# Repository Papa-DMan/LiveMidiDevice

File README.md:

# LiveMidiDevice
This repo merges my personal MIDI-Controller-DisplayDriver and MIDI-Controller repositories into this public one and also hosts the schematics and pcb designs for the project

The MIDI-Controller uses a tree and node structure. A FRDMK64F Dev board is the root of the tree and can handle up to two nodes right now. It utilizes the I2C bus with an extender chipset from TI to send data and power over an RJ45 8 connector cable down to the nodes that contain up to 8 buttons and 1 expression pedal and 1 led display controlled by and stm32 l412kb dev board.

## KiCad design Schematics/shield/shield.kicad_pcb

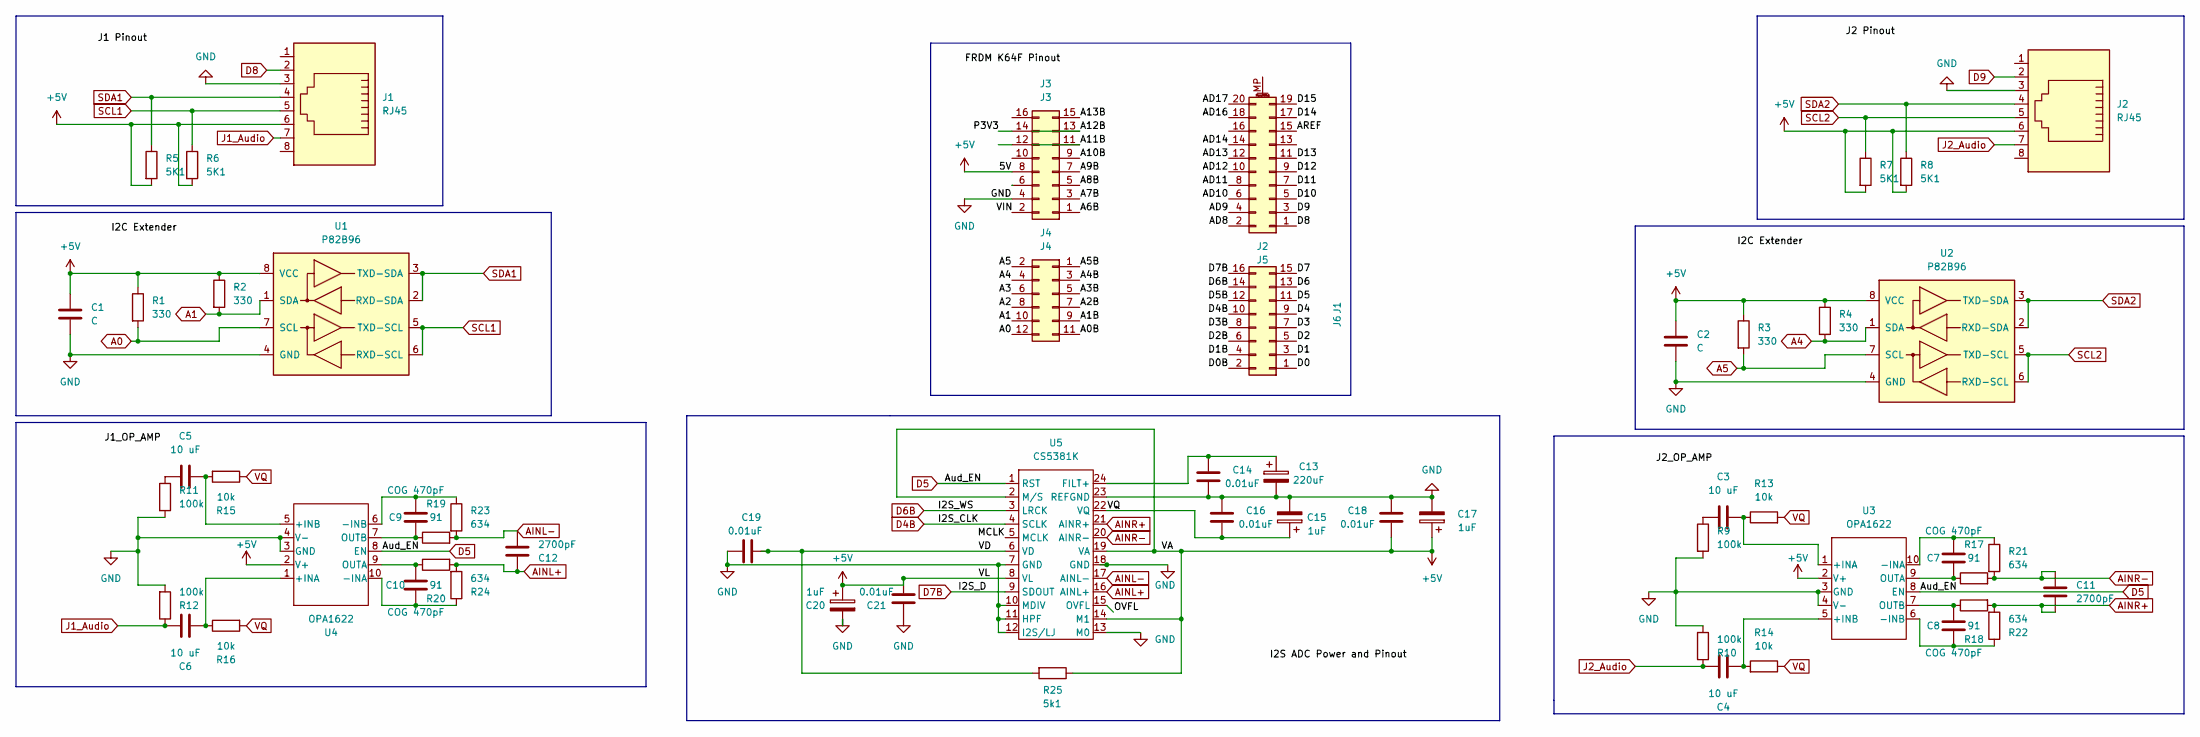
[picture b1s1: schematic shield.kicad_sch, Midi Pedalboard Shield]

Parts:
C1, C2: C; C_Disc_D3.0mm_W1.6mm_P2.50mm
C3, C4, C5, C6: 10 uF; CP_Radial_Tantal_D5.5mm_P5.00mm
C7, C8, C9, C10: COG 470pF; C_1812_4532Metric_Pad1.57x3.40mm_HandSolder
C11, C12: 2700pF; CP_Radial_D5.0mm_P2.50mm
C13: 220uF; C_1210_3225Metric_Pad1.33x2.70mm_HandSolder
C14, C16, C18, C19, C21: 0.01uF; C_0402_1005Metric_Pad0.74x0.62mm_HandSolder
C15, C17, C20: 1uF; C_0603_1608Metric_Pad1.08x0.95mm_HandSolder
J1, J2: RJ45; RJ45_Amphenol_RJHSE538X
J3: J3; PinHeader_2x08_P2.54mm_Vertical
J4: J4; PinHeader_2x06_P2.54mm_Vertical
J5: J2; PinHeader_2x10_P2.54mm_Vertical
J6: J1; PinHeader_2x08_P2.54mm_Vertical
R1, R2, R3, R4: 330; R_Axial_DIN0207_L6.3mm_D2.5mm_P2.54mm_Vertical
R5, R6, R7, R8: 5K1; R_Axial_DIN0207_L6.3mm_D2.5mm_P2.54mm_Vertical
R9, R10, R11, R12: 100k; R_Axial_DIN0207_L6.3mm_D2.5mm_P2.54mm_Vertical
R13, R14, R15, R16: 10k; R_Axial_DIN0207_L6.3mm_D2.5mm_P2.54mm_Vertical
R17, R18, R19, R20: 91; R_Axial_DIN0414_L11.9mm_D4.5mm_P5.08mm_Vertical
R21, R22, R23, R24: 634; R_1206_3216Metric_Pad1.30x1.75mm_HandSolder
R25: 5k1; R_Axial_DIN0207_L6.3mm_D2.5mm_P2.54mm_Vertical
U1, U2: P82B96; DIP-8_W7.62mm
U3, U4: OPA1622; Texas_S-PVSON-N10
U5: CS5381K; SOIC-24

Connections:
+5V: C1.1, C2.1, C17.1, C18.2, C20.1, C21.2, J1.6, J2.6, J3.8, R1.1, R2.1, R3.1, R4.1, R5.2, R6.2, R7.2, R8.2, R25.1, U1.8 (VCC), U2.8 (VCC), U3.2 (V+), U4.2 (V+), U5.2 (M/S), U5.8 (VL), U5.14 (M1), U5.19 (VA)
/A0B: J4.11
/A1B: J4.9
/A2: J4.8
/A2B: J4.7
/A3: J4.6
/A3B: J4.5
/A4B: J4.3
/A5B: J4.1
/A6B: J3.1
/A7B: J3.3
/A8B: J3.5
/A9B: J3.7
/A10B: J3.9
/A11B: J3.11
/A12B: J3.13
/A13B: J3.15
/AD8: J5.2
/AD9: J5.4
/AD10: J5.6
/AD11: J5.8
/AD12: J5.10
/AD13: J5.12
/AD14: J5.14
/AD16: J5.18
/AD17: J5.20
/AREF: J5.15
/D0: J6.1
/D0B: J6.2
/D1: J6.3
/D1B: J6.4
/D2: J6.5
/D2B: J6.6
/D3: J6.7
/D3B: J6.8
/D4: J6.9
/D5B: J6.12
/D6: J6.13
/D7: J6.15
/D10: J5.5
/D11: J5.7
/D12: J5.9
/D13: J5.11
/D14: J5.17
/D15: J5.19
/MCLK: U5.5 (MCLK)
/OVFL: U5.15 (OVFL)
/P3V3: J3.14
/VD: C19.1, R25.2, U5.6 (VD)
A0: J4.12, R1.2, U1.7 (SCL)
A1: J4.10, R2.2, U1.1 (SDA)
A4: J4.4, R4.2, U2.1 (SDA)
A5: J4.2, R3.2, U2.7 (SCL)
AINL+: C12.1, R20.2, R24.2, U5.16 (AINL+)
AINL-: C12.2, R19.2, R23.2, U5.17 (AINL-)
AINR+: C11.2, R18.2, R22.2, U5.21 (AINR+)
AINR-: C11.1, R17.2, R21.2, U5.20 (AINR-)
D4B: J6.10, U5.4 (SCLK)
D5: J6.11, U3.8 (EN), U4.8 (EN), U5.1 (RST)
D6B: J6.14, U5.3 (LRCK)
D7B: J6.16, U5.9 (SDOUT)
D8: J1.2, J5.1
D9: J2.2, J5.3
GND: C1.2, C2.2, C13.2, C14.2, C15.2, C16.1, C17.2, C18.1, C19.2, C20.2, C21.1, J1.3, J2.3, J3.4, R9.2, R10.2, R11.2, R12.2, U1.4 (GND), U2.4 (GND), U3.3 (GND), U3.4 (V-), U4.3 (GND), U4.4 (V-), U5.7 (GND), U5.10 (MDIV), U5.11 (HPF), U5.12 (I2S/LJ), U5.13 (M0), U5.18 (GND), U5.23 (REFGND)
J1_Audio: C6.1, J1.7, R12.1
J2_Audio: C4.1, J2.7, R10.1
unnamed: C3.1, R9.1
unnamed: C3.2, R13.1, U3.1 (+INA)
unnamed: C4.2, R14.2, U3.5 (+INB)
unnamed: C5.1, R11.1
unnamed: C5.2, R15.2, U4.5 (+INB)
unnamed: C6.2, R16.1, U4.1 (+INA)
unnamed: C7.1, R17.1, U3.9 (OUTA)
unnamed: C7.2, R21.1, U3.10 (-INA)
unnamed: C8.1, R18.1, U3.7 (OUTB)
unnamed: C8.2, R22.1, U3.6 (-INB)
unnamed: C9.1, R19.1, U4.7 (OUTB)
unnamed: C9.2, R23.1, U4.6 (-INB)
unnamed: C10.1, R20.1, U4.9 (OUTA)
unnamed: C10.2, R24.1, U4.10 (-INA)
unnamed: C13.1, C14.1, U5.24 (FILT+)
SCL1: J1.5, R6.1, U1.5 (TXD-SCL), U1.6 (RXD-SCL)
SCL2: J2.5, R7.1, U2.5 (TXD-SCL), U2.6 (RXD-SCL)
SDA1: J1.4, R5.1, U1.2 (RXD-SDA), U1.3 (TXD-SDA)
SDA2: J2.4, R8.1, U2.2 (RXD-SDA), U2.3 (TXD-SDA)
VQ: C15.1, C16.2, R13.2, R14.1, R15.1, R16.2, U5.22 (VQ)

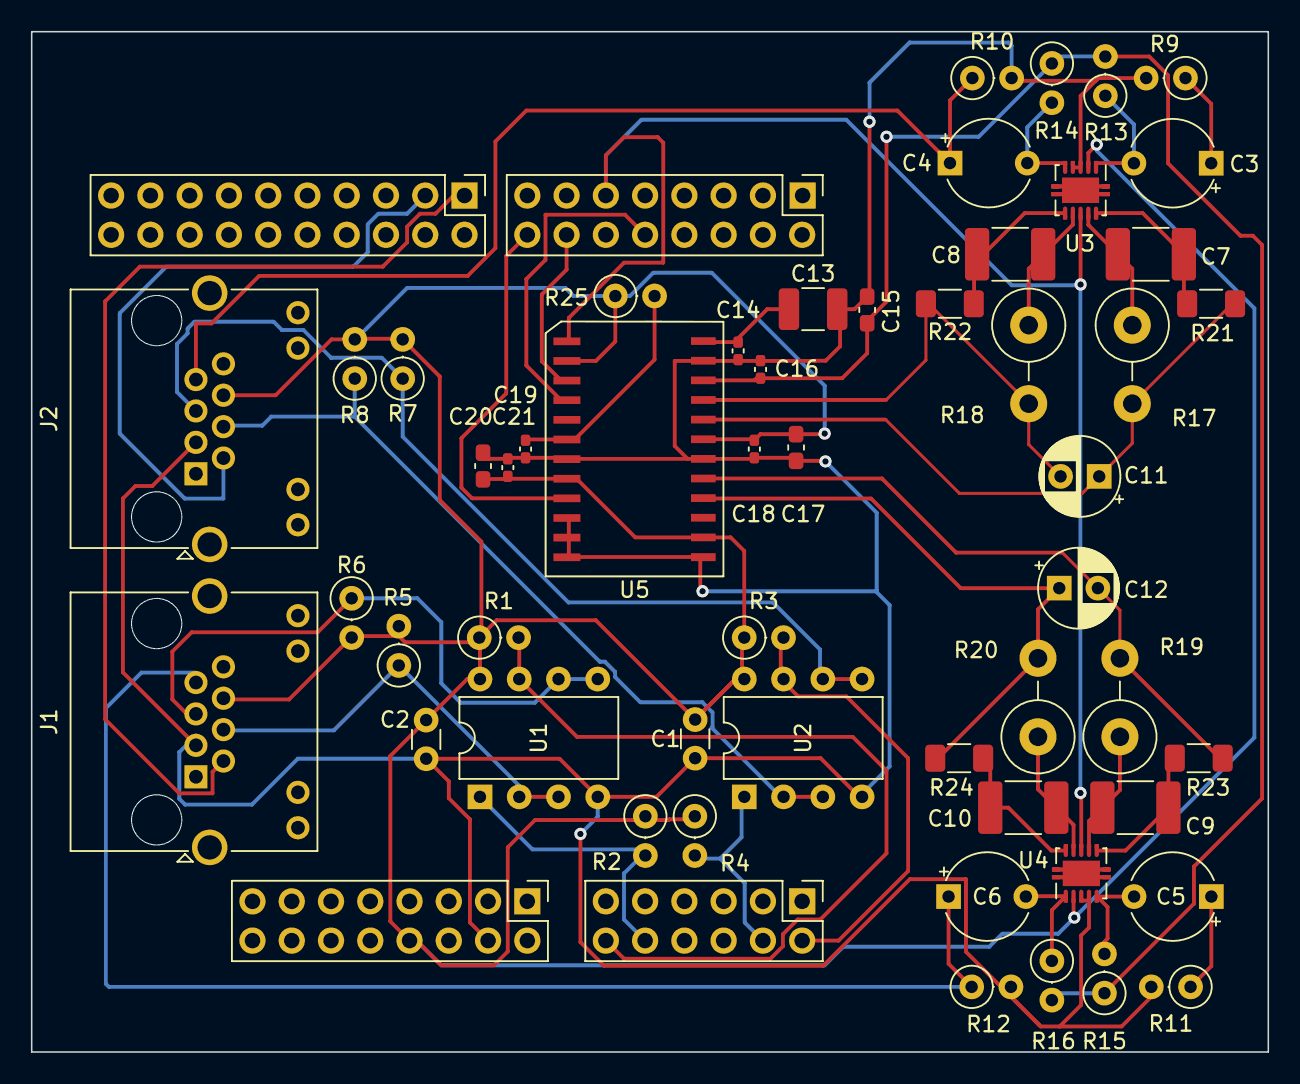
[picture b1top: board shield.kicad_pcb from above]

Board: 2 copper layers, 80.0 x 66.0 mm, 57 parts (0 on the bottom side), 39 nets.

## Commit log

2023-02-28 Inital Commit
2023-02-28 added schematics
2023-03-03 update schematic
2023-03-03 Fixed Schematic. The FRDM K64F pin positions were one step too wide so narrowed and updated tracks. The pads for the I2S ADC IC were too narrow so wided to the maximum Spec. Updated Silkscreen to be 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
2023-03-08 Update Gerber Zip
2023-03-15 generated .cad and stencil files for fab
